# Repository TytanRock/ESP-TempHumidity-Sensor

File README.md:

# ESP Based IoT reporter
Project and Source files for custom PCB that implements various sensors with an ESP for reporting

## Sponsored by PCBWay
This project was graciously sponsored by [PCBWay](https://www.pcbway.com/) who provided boards of the product. I've used them before and enjoy their service, as they provide an affordable way of creating professional PCBs for projects such as this one. Check them out!

## Purpose
This is mostly a learning exercise for more complex boards, and tighter integration with cloud stuff.
I wanted to make a board that uses an ESP8266 to measure various things and report them to a cloud service.
This first version includes just measuring temperature and humidity throughout the house, with the option to expand and measure other things through I2C or Analog.

It includes an FTDI chip to program the ESP, the ESP itself, a temp/humidity sensor, and a Lithium-Ion charger with a connector for a Li-ion battery if I want to place it somewhere out of reach.
The repo will also include source code once I get my first batch of boards in.

## Board Views
I don't have the physical boards currently, but I think it's always nice to see what the boards look like without downloading and viewing it through eagle.
So here's the Top and Bottom boardview from Eagle.

Have fun with it if you think it's cool.

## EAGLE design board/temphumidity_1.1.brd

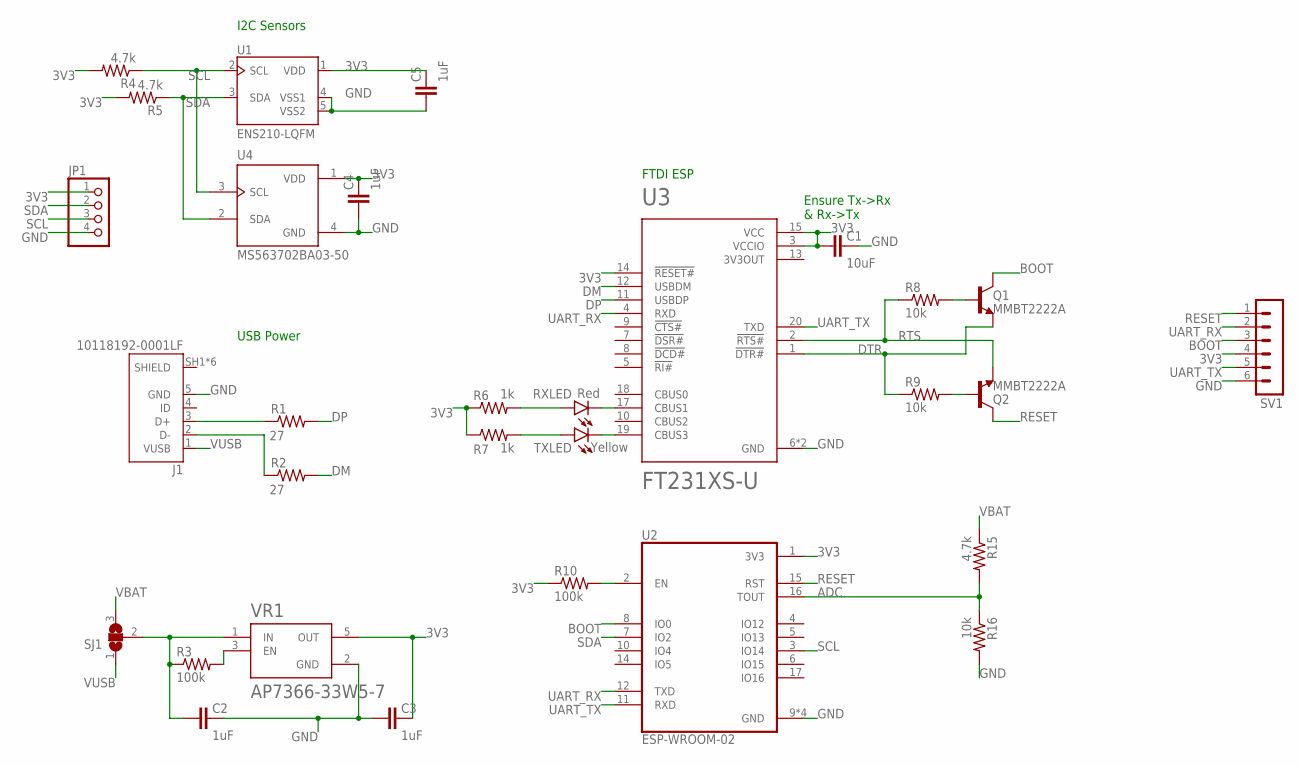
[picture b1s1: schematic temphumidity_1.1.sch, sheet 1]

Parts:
C1: 10uF; C0805
C2, C3, C4, C5: 1uF; C0805
J1: 10118192-0001LF; AMPHENOL_10118192-0001LF
JP1: PINHD-1X4; 1X04
Q1, Q2: MMBT2222A; SOT23
R1, R2: 27; R0805
R3, R10: 100k; R0805
R4, R5, R15: 4.7k; R0805
R6, R7: 1k; R0805
R8, R9, R16: 10k; R0805
RXLED: Red; CHIP-LED0805
SJ1: SJ2W; SJ_2
SV1: MA06-1
TXLED: Yellow; CHIP-LED0805
U1: ENS210-LQFM; SON95P200X200X80-5N160X70
U2: ESP-WROOM-02; MODULE_ESP-WROOM-02
U3: FT231XS-U; SOP63P600X175-20N
U4: MS563702BA03-50; TE_MS563702BA03-50
VR1: AP7366-33W5-7; SOT95P285X140-5N

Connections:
3V3: C1.2, C3.1, C4.1, C5.1, JP1.1, R4.2, R5.2, R6.1, R7.1, R10.1, SV1.4, U1.1 (VDD), U2.1 (3V3), U3.3 (VCCIO), U3.14 (!RESET#), U3.15 (VCC), U4.1 (VDD), VR1.5 (OUT)
3V3OUT: U3.13 (3V3OUT)
ADC: R15.2, R16.1, U2.16 (TOUT)
BOOT: Q1.3 (C), SV1.3, U2.8 (IO0)
DM: R2.2, U3.12 (USBDM)
DP: R1.2, U3.11 (USBDP)
DTR: Q1.2 (E), R9.1, U3.1 (!DTR#)
GND: C1.1, C2.1, C3.2, C4.2, C5.2, J1.5 (GND), JP1.4, R16.2, SV1.6, U1.4 (VSS1), U1.5 (VSS2), U2.9 (GND), U2.13 (GND), U2.18 (GND), U2.19 (GND), U3.6 (GND), U3.16 (GND), U4.4 (GND), VR1.2 (GND); also elsewhere on the board
unnamed: J1.3 (D+), R1.1
unnamed: J1.2 (D-), R2.1
unnamed: R3.2, VR1.3 (EN)
unnamed: RXLED.C, U3.17 (CBUS1)
unnamed: TXLED.C, U3.19 (CBUS3)
unnamed: R6.2, RXLED.A
unnamed: R7.2, TXLED.A
unnamed: Q1.1 (B), R8.2
unnamed: Q2.1 (B), R9.2
unnamed: R10.2, U2.2 (EN)
RESET: Q2.3 (C), SV1.1, U2.15 (RST)
RTS: Q2.2 (E), R8.1, U3.2 (!RTS#)
SCL: JP1.3, R4.1, U1.2 (SCL), U2.3 (IO14), U4.3 (SCL)
SDA: JP1.2, R5.1, U1.3 (SDA), U2.7 (IO2), U4.2 (SDA)
SELECTEDVOLTAGE: C2.2, R3.1, SJ1.2, VR1.1 (IN)
UART_RX: SV1.2, U2.12 (TXD), U3.4 (RXD)
UART_TX: SV1.5, U2.11 (RXD), U3.20 (TXD)
VBAT: R15.1, SJ1.3; also elsewhere on the board
VUSB: J1.1 (VUSB), SJ1.1; also elsewhere on the board

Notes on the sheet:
Ensure Tx->Rx & Rx->Tx
USB Power
FTDI ESP
I2C Sensors

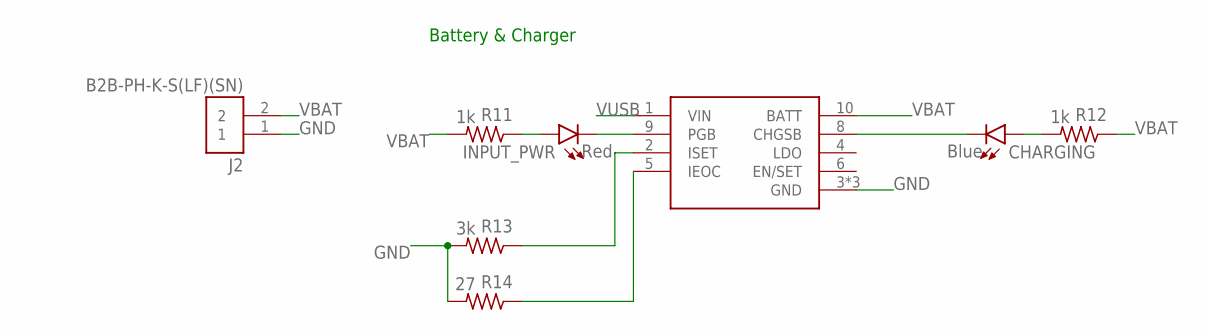
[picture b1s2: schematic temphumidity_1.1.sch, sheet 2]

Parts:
CHARGING: Blue; CHIP-LED0805
INPUT_PWR: Red; CHIP-LED0805
J2: B2B-PH-K-S(LF)(SN); JST_B2B-PH-K-S(LF)(SN)
R11, R12: 1k; R0805
R13: 3k; R0805
R14: 27; R0805
U$2: RT9532GQW; SON50P300X300X80-11N

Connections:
GND: J2.1, R13.2, R14.2, U$2.3 (GND), U$2.7 (GND), U$2.11 (GND); also elsewhere on the board
unnamed: INPUT_PWR.C, U$2.9 (PGB)
unnamed: CHARGING.C, U$2.8 (CHGSB)
unnamed: INPUT_PWR.A, R11.1
unnamed: R13.1, U$2.2 (ISET)
unnamed: CHARGING.A, R12.2
unnamed: R14.1, U$2.5 (IEOC)
VBAT: J2.2, R11.2, R12.1, U$2.10 (BATT); also elsewhere on the board
VUSB: U$2.1 (VIN); also elsewhere on the board

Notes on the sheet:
Battery & Charger

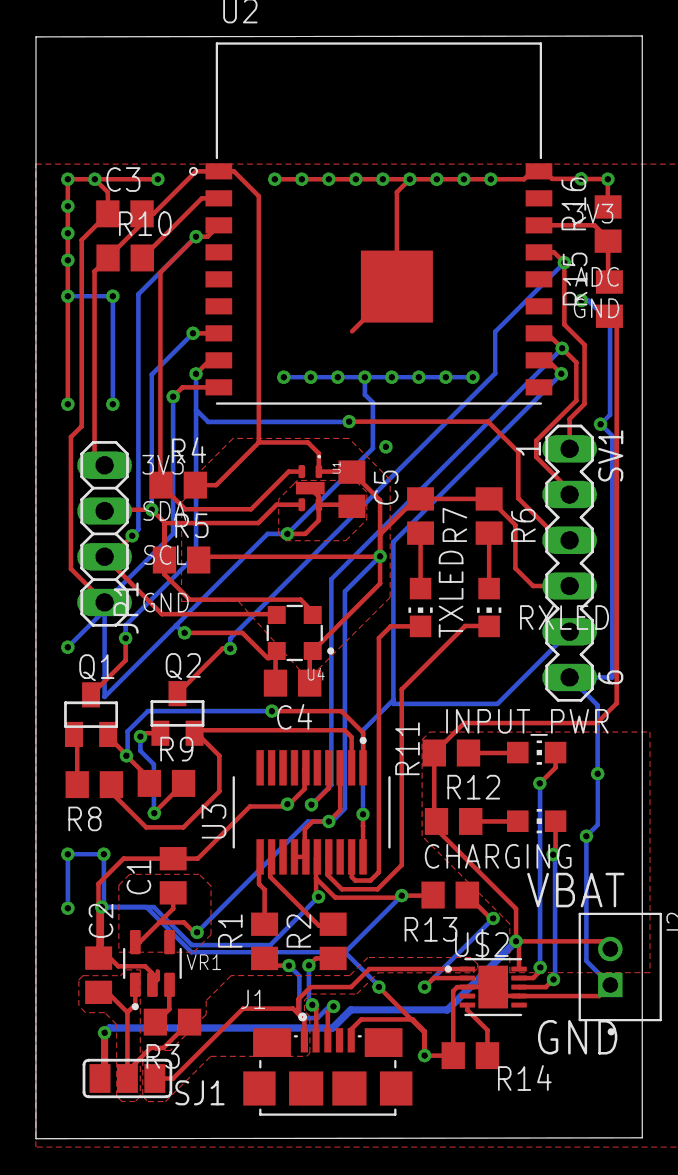
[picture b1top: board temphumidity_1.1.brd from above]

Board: 2 copper layers, 33.7 x 61.3 mm, 38 parts (0 on the bottom side), 32 nets.

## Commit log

2021-08-22 Initial Commit
    V1.0 sent out to PCBway for production
2021-08-22 Added bom for v1.0
2021-08-22 Moved board docs to board subdirectory & added website code
2021-08-22 Moved readme back out to root
2021-08-22 Added barebones to web project
2021-08-22 Update gradle.yml
    Fix change from backend -> website
2021-08-23 Removed eagle backup files to clean up repo
2021-08-23 Refactored and broke master
    Didn't realize I was committing a filename change
2021-08-24 Fixed spotless issue
2021-08-24 Various more work for baseline stuff
2021-08-24 Dockerfile added
2021-08-24 Added a main interface so I can test the site
2021-08-24 Added deploy & renamed some jobs
2021-08-24 Update Dockerfile
2021-08-25 Did some revisions to beef up connection pathways and reduce radiation
    Further work will be done on 1.1 until I get the boards in and can make
    decisions on what major things to change
2021-08-25 Added Sponsorship Snippet
    PCBWay contacted me to ask if I wanted them to sponsor this project, and I did. So I added this.
2021-08-28 More revisions on 1.1, added pictures for Readme
2021-08-29 Wrote spring application to make use of sql database
2021-08-29 Removed BootRun Test
    Won't work without a SQL server running alongside
2021-08-29 Changed infoGatherer to be a little nicer
2021-08-29 Specified tablenames and added debug message
2021-09-02 More board work
2021-09-02 Added breakout so old programmers can program new boards
